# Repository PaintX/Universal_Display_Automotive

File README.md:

# Universal_Display_Automotive
Affichage Universel a encaster diam 48 pour boitier diam 50 in 52 out

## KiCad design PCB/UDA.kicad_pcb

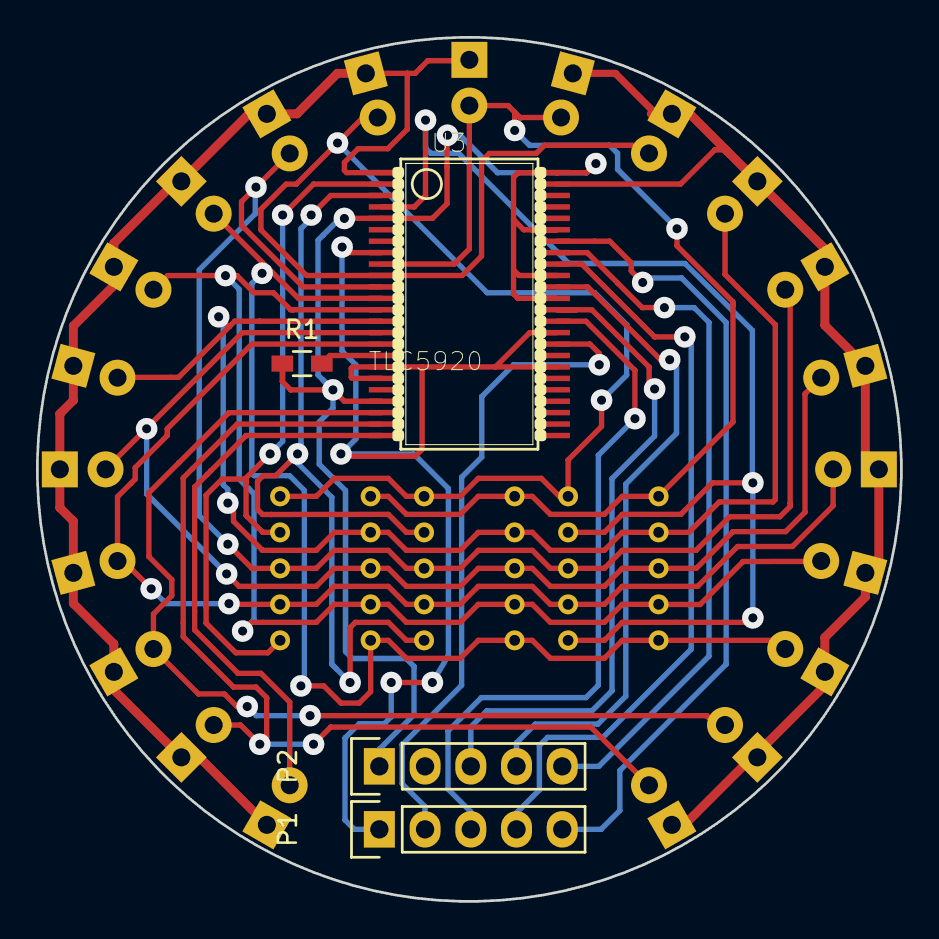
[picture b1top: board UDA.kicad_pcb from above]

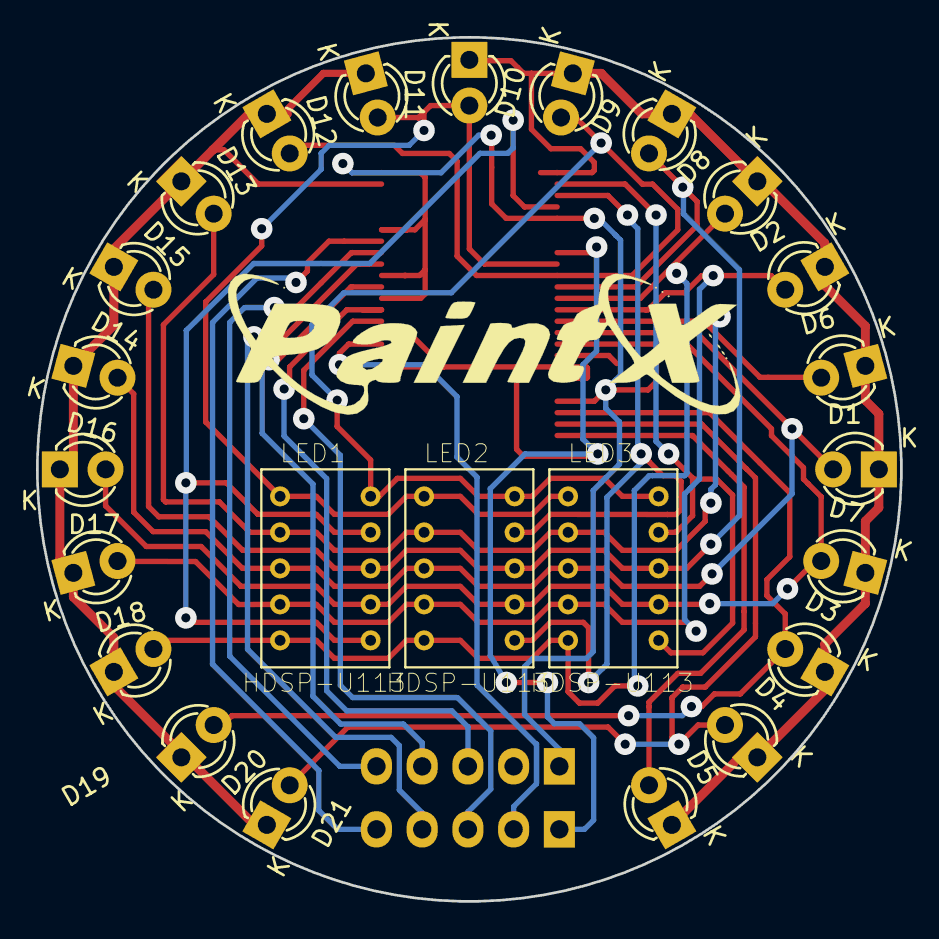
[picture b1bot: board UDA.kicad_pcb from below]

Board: 2 copper layers, 48.0 x 48.0 mm, 28 parts (24 on the bottom side), 26 nets.

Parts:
D1, D2, D3, D4, D5, D6, D7, D8, D9, D10, D11, D12, D13, D14, D15, D16, D17, D18, D19, D20, D21: LED; LED-3MM
LED1, LED2, LED3: HDSP-U113
P1, P2: CONN_01X05; Pin_Header_Straight_1x05
R1: 0.0; R_0603_HandSoldering
U3: TLC5920; SSOP48DL

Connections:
+5V: P1.1, U3.8, U3.18, U3.19, U3.31, U3.34
COM0: LED1.6, LED1.9, U3.4
COM1: LED2.6, LED2.9, U3.3
COM2: LED3.6, LED3.9, U3.2
COM3: D1.1, D2.1, D3.1, D4.1, D5.1, D6.1, D7.1, D8.1, D9.1, D10.1, D11.1, U3.1
COM4: D12.1, D13.1, D14.1, D15.1, D16.1, D17.1, D18.1, D19.1, D20.1, D21.1, U3.47
CSEL0: P2.4, U3.38
CSEL1: P2.3, U3.36
CSEL2: P1.3, U3.35
DSEL: P1.2, U3.33
GND: P2.1, R1.1, U3.5, U3.21, U3.37, U3.39, U3.43, U3.48
LATCH: P2.5, U3.41
unnamed: R1.2, U3.17
S0: D11.2, D12.2, LED1.1, LED2.1, LED3.1, U3.9
S1: D10.2, D13.2, LED1.10, LED2.10, LED3.10, U3.10
S2: D9.2, D14.2, LED1.8, LED2.8, LED3.8, U3.11
S3: D8.2, D19.2, LED1.5, LED2.5, LED3.5, U3.12
S4: D2.2, D18.2, LED1.4, LED2.4, LED3.4, U3.13
S5: D6.2, D15.2, LED1.2, LED2.2, LED3.2, U3.14
S6: D1.2, D16.2, LED1.3, LED2.3, LED3.3, U3.15
S7: D7.2, D17.2, LED1.7, LED2.7, LED3.7, U3.16
S8: D3.2, D20.2, U3.22
S9: D4.2, D21.2, U3.23
S10: D5.2, U3.24
SCLK: P1.4, U3.40
SIN: P1.5, U3.42

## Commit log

2015-09-17 Create README.md
    Create README.md
2015-09-17 - Ajout premier PCB
2015-09-17 - version finale restante a router
2015-09-17 - routage casiement fini
2015-09-18 - creation du module en 3D pour future utilisation
2015-09-21 - fin du routage
2015-10-07 - Correction sur le point des afficheurs 7 segments
2015-10-08 - ajout d'une libraire pour piloter l'affichage avec un arduino ou autre
2015-10-08 - implantation de la configration des pins
2015-10-08 - ajout mode point ou ligne
2015-10-09 - correction du driver
2016-01-08 - corection mineure
